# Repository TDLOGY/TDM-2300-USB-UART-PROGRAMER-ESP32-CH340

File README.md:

---
#### Mạch USB Uart CH340 kết hợp chân nạp IO0 và RST cho chip ESP32 với cơ chế tự nạp và reset, dùng như usb uart và nạp với kích thước nhỏ gọn, cổng USB-C siêu bền nhé.
---
__Link mua hàng :)__

- __[Shopee xem tại dây](
https://shopee.vn/product/364070088/22227537765/)__ - USB-C programer mini for ESP8266, ESP32
- __[Linhkienthuduc.com tại đây](https://linhkienthuduc.com/usb-uart-kiem-mach-nap-esp32-esp8266-cong-type-c-v1)__ - Mua các mặt hàng do TDMAKER sản xuất hoặc các sản phẩm ESP32 ở shop với hóa đơn trên 200k inbox zalo để được tặng 1 cái test thử nhé!

You will like those projects!

--- 

Driver download: http://www.wch.cn/download/CH341SER_ZIP.html

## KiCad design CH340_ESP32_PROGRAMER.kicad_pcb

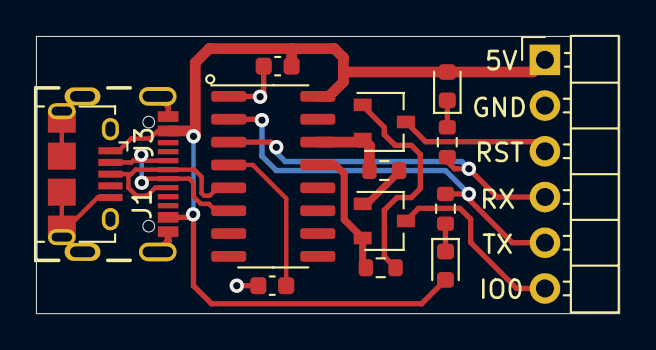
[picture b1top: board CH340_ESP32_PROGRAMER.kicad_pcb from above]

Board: 2 copper layers, 32.4 x 15.4 mm, 14 parts (0 on the bottom side), 15 nets.

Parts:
C1: 1uF/16V; C_0603_1608Metric
C2: 100nF/16V; C_0603_1608Metric
J1: USB4105-GF-A; GCT_USB4105-GF-A
J2: Conn_01x06_Male; PinHeader_1x06_P2.54mm_Horizontal
J3: USB_B_Micro; USB_Micro-B_Amphenol_10118194_Horizontal
Q1, Q2: BC817; SOT-23
R1, R2, R3, R4: 4K7; R_0603_1608Metric
RX1: LED; LED_0603_1608Metric
TX1: LED; LED_0603_1608Metric
U1: CH340C; SOIC-16_3.9x9.9mm_P1.27mm

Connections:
+5V: C1.2, J1.A4_B9 (VBUS), J1.B4_A9 (VBUS), J2.1, J3.1 (VBUS), RX1.2 (A), TX1.2 (A), U1.16 (VCC)
D+: J1.A6 (DP1), J1.B6 (DP2), J3.3 (D+), U1.5 (UD+)
D-: J1.A7 (DN1), J1.B7 (DN2), J3.2 (D-), U1.6 (UD-)
GND: C1.1, C2.1, J1.A1_B12 (GND), J1.B1_A12 (GND), J1.S1 (SHELL_GND), J1.S2 (SHELL_GND), J1.S3 (SHELL_GND), J1.S4 (SHELL_GND), J2.2, J3.5 (GND), J3.6 (Shield), U1.1 (GND)
unnamed: C2.2, U1.4 (V3)
unnamed: J2.3, Q1.3 (C)
unnamed: J2.4, R4.2, U1.3 (RXD)
unnamed: J2.5, R1.2, U1.2 (TXD)
unnamed: J2.6, Q2.3 (C)
unnamed: Q1.1 (B), R2.1
unnamed: Q1.2 (E), R3.2, U1.14 (~RTS)
unnamed: Q2.1 (B), R3.1
unnamed: Q2.2 (E), R2.2, U1.13 (~DTR)
unnamed: R1.1, TX1.1 (K)
unnamed: R4.1, RX1.1 (K)

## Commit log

2023-03-11 Schematic
2023-03-11 Kicad Design file
